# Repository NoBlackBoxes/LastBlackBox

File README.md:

# The Last Black Box

> - Do you depend on technology to work? to learn? to socialize?
> - Do you want to know what is going on inside the machines that run your life?
> - Do you want to be ready for the coming era of AI?

## Summary

Imagine a world without "black boxes". A world where you understand how your tools work and can use them to do what you want.

This world is much closer than you realize, and we have developed this training course to help get you there as quickly (and enjoyably!) as possible.

**The Last Black Box** is a hands-on introduction to the foundations of modern technology<p>...from ***electrons*** to ***AI***.

## Principles

----

<p align="center" style="font-size:32px">
<a href="course/README.md" style="color: #FFFF00; background: #000000; border-color: #FFFF00; border-style: solid; border-width: 2px; border-radius:6px; padding-left:12px; padding-right:12px;"><b>Start the course!</b></a>
</p>

----

## License

<br />The entire LastBlackBox repository and website is licensed under a <a rel="license" href="http://creativecommons.org/licenses/by-nc-sa/4.0/">Creative Commons Attribution-NonCommercial-ShareAlike 4.0 International License</a>.

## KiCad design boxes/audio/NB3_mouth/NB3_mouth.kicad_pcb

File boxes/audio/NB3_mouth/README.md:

# Audio : NB3_mouth

PCB design and fabrication for NB3 mouth, a mono i2s DAC and Amplifier

## Parts

- MAX98357A from Maxim: [datasheet](libraries/parts/I2S_DAC-AMP_MAX98357A/I2S_DAC-AMP_MAX98357A.pdf)

## Fabrication

### Generate files
0. Save front/back renders and 3D model (step)
1. Create "fab" folder in KiCAD project root
2. Export BOM (as CSV): File->Fabrication outputs->BOM
3. Edit BOM: Open as ODS and save as XLSX in "fab" folder
4. Generate Gerbers: File->Fabrication outputs->Gerbers [settings](NB3_mouth_FAB_plot_settings.png)
5. Generate Drill: File->Fabrication outputs->Drill Files [settings](NB3_mouth_FAB_drill_settings.png)
6. Generate Centroids: File->Fabrication outputs->Componenet Placement [settings](NB3_mouth_FAB_pos_settings.png)
7. Zip entire fab folder (including BOM.xlsx)

### Upload boards(s) - PCBWay

#### Assembly Service
- Service: Turnkey Assembly
- Board type: Panelized PCBs
- Assembly: Both Sides
- Quantity: *200*

##### Other Parameters
- Number of unique Parts: 6
- Number of SMD Parts: 6
- Number of BGA/QFP Parts: 1
- Number of Through-Hole Parts: 1
			
#### PCB Specifications
- Board type: Panel by PCBWay
- Panel requirements: Panel in 2*4, total 25 panels=total 200 individual boards.
- Route Process: Panel as Tab Route
- X-out Allowance in Panel: Accept
- Different design in panel: 1
- Size: 56 x 78 mm
- Quantity: 20
- Layer: 2 Layers
- Material: FR-4: TG150-160
- Thickness: 1.6 mm
- Min track/spacing: 6/6mil
- Min hole size: 0.3mm
- Solder mask: White
- Silkscreen: Black
- Edge connector: No
- Surface finish: Immersion gold(ENIG) (1U"), "HASL" to "ENIG" No
- Via process: Tenting vias
- Finished copper: 1 oz Cu
- Remove product No.: No

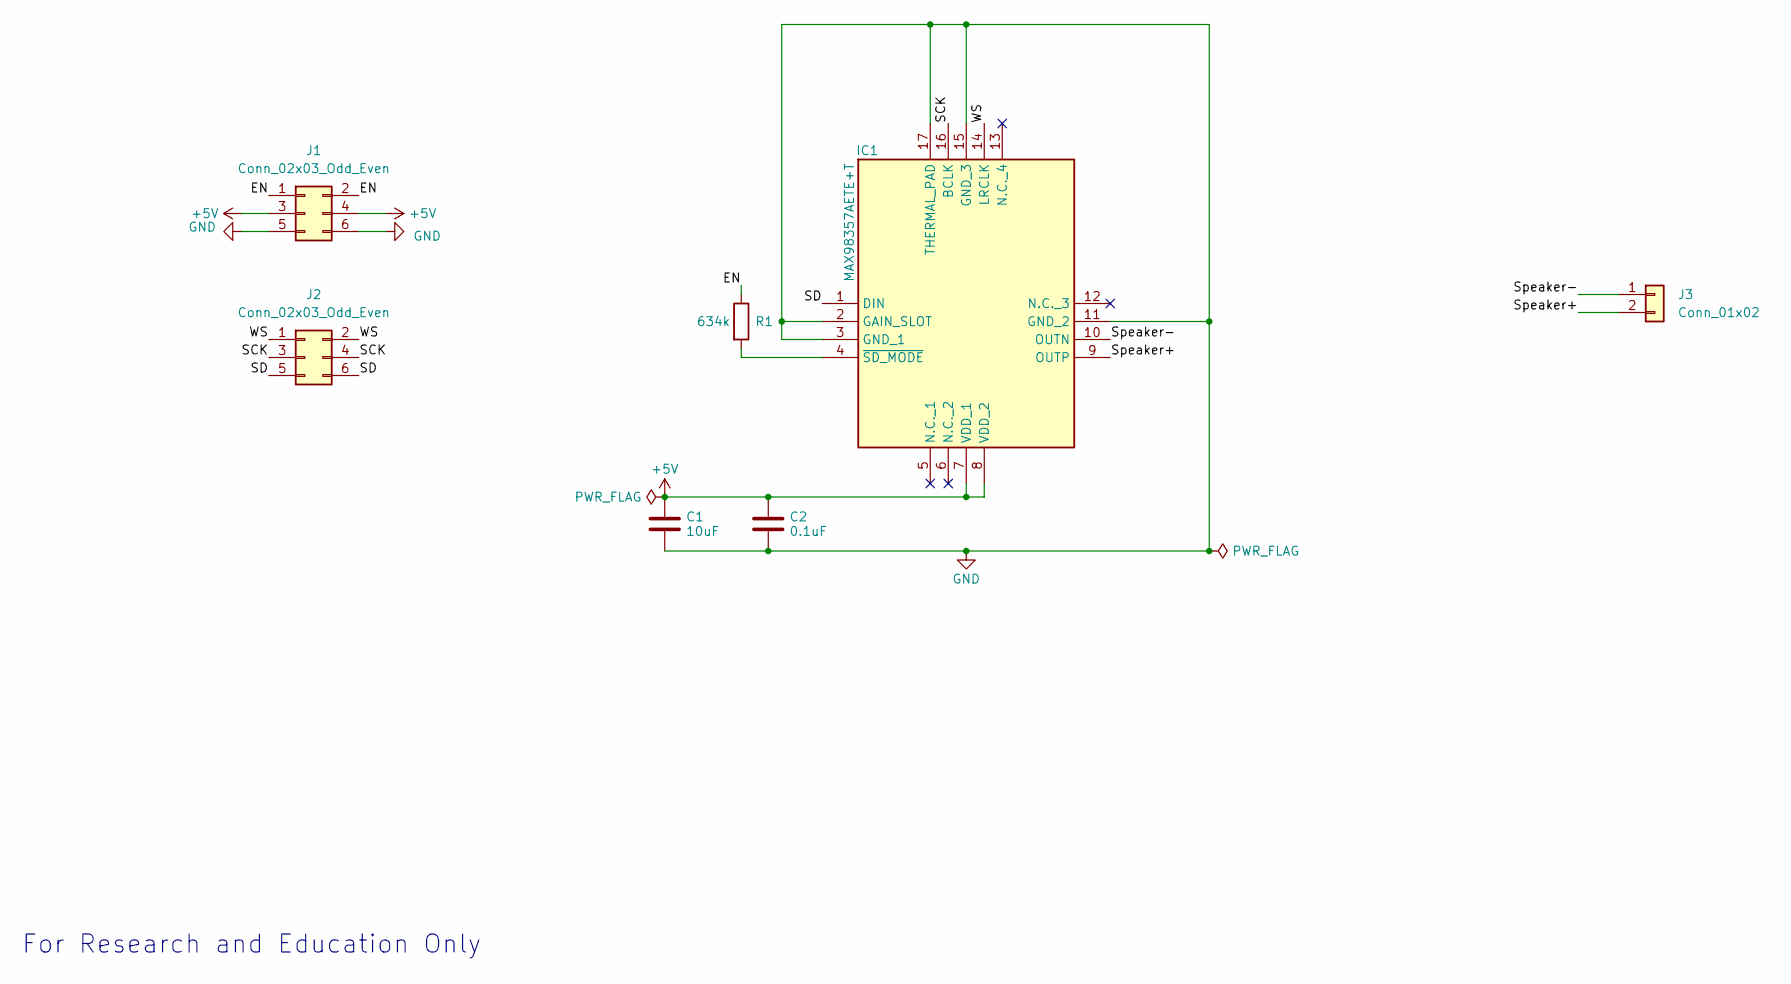
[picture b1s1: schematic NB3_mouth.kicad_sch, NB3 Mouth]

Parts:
C1: 10uF; C_0805_2012Metric
C2: 0.1uF; C_0402_1005Metric
IC1: MAX98357AETE+T; I2S_DAC-AMP_MAX98357A; Mouser Part Number 700-MAX98357AETE+T
J1, J2: Conn_02x03_Odd_Even; PinHeader_2x03_P2.54mm_Vertical_SMD
J3: Conn_01x02; PinHeader_1x02_P2.54mm_Horizontal
R1: 634k; R_0402_1005Metric

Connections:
+5V: C1.1, C2.1, IC1.7 (VDD_1), IC1.8 (VDD_2), J1.3, J1.4
/EN: J1.1, J1.2, R1.1
/SCK: IC1.16 (BCLK), J2.3, J2.4
/SD: IC1.1 (DIN), J2.5, J2.6
/Speaker+: IC1.9 (OUTP), J3.2
/Speaker-: IC1.10 (OUTN), J3.1
/WS: IC1.14 (LRCLK), J2.1, J2.2
GND: C1.2, C2.2, IC1.2 (GAIN_SLOT), IC1.3 (GND_1), IC1.11 (GND_2), IC1.15 (GND_3), IC1.17 (THERMAL_PAD), J1.5, J1.6
unnamed: IC1.4 (~SD_MODE), R1.2

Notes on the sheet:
For Research and Education Only

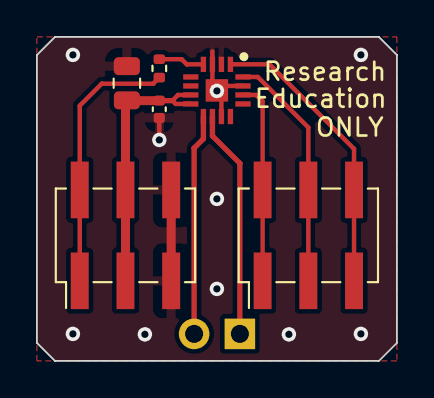
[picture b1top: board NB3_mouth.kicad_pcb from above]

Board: 2 copper layers, 20.0 x 18.0 mm, 7 parts (1 on the bottom side), 9 nets.

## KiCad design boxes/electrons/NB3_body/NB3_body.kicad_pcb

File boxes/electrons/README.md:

# The Last Black Box : Electrons
In this box, you will learn about electrons...

<details><summary><i>Materials</i></summary><p>

Name|Description| # |Package|Data|Link|
:-------|:----------|:-----:|:-:|:--:|:--:|
NB3 Body|NB3 robot base PCB|1|Body (000)|[-D-](/boxes/electrons/NB3_body)|[-L-](VK)
Resistor (470)|470 &Omega;/0.25 W|2|Passive Electronics|[-D-](/boxes/electrons/_resources/datasheets/resistor.pdf)|[-L-](https://uk.farnell.com/multicomp/mf25-470r/res-470r-1-250mw-axial-metal-film/dp/9341943)
Resistor (1k)|1 k&Omega;/0.25 W|2|Passive Electronics|[-D-](/boxes/electrons/_resources/datasheets/resistor.pdf)|[-L-](https://uk.farnell.com/multicomp/mf25-1k/res-1k-1-250mw-axial-metal-film/dp/9341102)
Resistor (10k)|10 k&Omega;/0.25 W|2|Passive Electronics|[-D-](/boxes/electrons/_resources/datasheets/resistor.pdf)|[-L-](https://uk.farnell.com/multicomp/mf25-10k/res-10k-1-250mw-axial-metal-film/dp/9341110)
Button|Tactile switch|2|Passive Electronics|[-D-](/boxes/electrons/_resources/datasheets/button.pdf)|[-L-](https://uk.farnell.com/omron/b3f-1000/switch-spno-0-05a-24v-tht-0-98n/dp/176432)
Potentiometer|2.2 k&Omega; variable resistor|2|Passive Electronics|[-D-](/boxes/electrons/_resources/datasheets/pot_2k2.pdf)|[-L-](https://uk.farnell.com/bourns/3362p-1-222lf/trimmer-pot-2-2kohm-10-1turn-th/dp/2328599)
Breadboard (400)|400-tie solderless breadboard|1|Small (010)|[-D-](/boxes/electrons/_resources/datasheets/breadboard_400.pdf)|[-L-](https://www.amazon.co.uk/gp/product/B0739XRX8F)
Breadboards (170)|170-tie solderless breadboard|4|Small (010)|[-D-](/boxes/electrons/_resources/datasheets/breadboard_170.pdf)|[-L-](https://www.amazon.co.uk/ELEGOO-tie-points-Breadboard-Breadboards-Electronic/dp/B01N0YWIR7)
Batteries (AA)|AA 1.5 V alkaline battery|4|Auxiliary|[-D-](/boxes/electrons/)|[-L-](https://www.amazon.co.uk/Duracell-Optimum-Alkaline-Batteries-MX1500/dp/B093Q5XY66)
Battery holder|4xAA battery holder with ON-OFF switch|1|Small (010)|[-D-](/boxes/electrons/)|[-L-](https://www.amazon.co.uk/gp/product/B0814ZH68F)
Jumper Kit|Kit of multi-length 22 AWG breadboard jumpers|1|Large (100)|[-D-](/boxes/electrons/_resources/datasheets/jumper_kit.pdf)|[-L-](https://uk.farnell.com/multicomp/mc001810/hard-jumper-wire-22awg-140pc/dp/2770338)
Jumper Wires|Assorted 22 AWG jumper wire leads (male/female)|1|Cables (001)|[-D-](/boxes/electrons/_resources/datasheets/jumper_wires.pdf)|[-L-](https://www.amazon.co.uk/gp/product/B09KR7Z4PF)
Test Lead|Alligator clip to 0.64 mm pin (20 cm)|2|Cables (001)|[-D-](/boxes/electrons/)|[-L-](https://www.amazon.co.uk/gp/product/B096JR15JW)
Rubber feet|Adhesive rubber standoffs (1421T6CL)|4|Passive Electronics|[-D-](/boxes/electrons/_resources/datasheets/rubber_feet.pdf)|[-L-](https://uk.farnell.com/hammond/1421t6cl/feet-stick-on-pk24/dp/1876522)
Capacitor (small)|0.1 uF ceramic capacitor|1|Passive Electronics|[-D-](/boxes/electrons/_resources/datasheets/capacitor_ceramic.pdf)|[-L-](https://uk.farnell.com/kemet/c322c104k1r5ta/cap-0-1-f-100v-10-x7r/dp/1457685)
Capacitor (large)|100 uF aluminum electrolytic capacitor|1|Passive Electronics|[-D-](/boxes/electrons/_resources/datasheets/capacitor_electrolytic.pdf)|[-L-](https://uk.farnell.com/rubycon/16zlh100mefc5x11/cap-100-f-16v-20/dp/8126283)

</p></details><hr>

## Electrons
#### Watch this video: [Electric Fields](https://vimeo.com/1032441712)
<p align="center">

</p>

> A very useful, and quite simple, depiction of the lines of force surrounding charged particles.

- Draw the electric field around a negative charge and positive charge separated by a small distance. Use the following image as a starting point.

#### Watch this video: [Voltage](https://vimeo.com/1000730032)
<p align="center">

</p>

> When there is more negative or positive charge in one location vs. another there is a *potential difference* between these locations. This *potential difference* is called a **voltage** and it creates a pressure that pushes electrons from the location with more negative charge to the location with less.

#### Watch this video: [Conductors](https://vimeo.com/1029337222)
<p align="center">

</p>

> Some materials have electrons in their outer orbitals that are happy to jump between neighboring atomic nuclei (of the same element). These electrons are "free" to move around the material. If we place such a material between two locations with a *potential difference* (voltage), then electrons will flow from the **(-)** location to the **(+)** location; the material will **conduct** electricity.

#### Watch this video: [Batteries](https://vimeo.com/1029278169)
<p align="center">

</p>

> Generating a stable voltage requires a renewable source of electrons to maintain a *potential difference*. We can accomplish this with a (redox) chemical reaction inside the wonderfully useful device that we call a **battery**.

- **TASK**: Measure the voltage of a AA battery using your multimeter.
  - *Hint*: Select the voltage ("V") setting and touch your probes to either end of the battery. Depending on your multimeter, you may also need to select an appropriate "range". For a single AA battery, you should expect to measure between 1 and 2 Volts.
  - *Help*: If you are new to using a multimeter, then I recommend that you watch this video: [NB3-Multimeter Basics](https://vimeo.com/1027764019)
  - *Help*: If you are new to measuring voltage with a multimeter, then I recommend that you watch this video: [NB3-Measuring Voltage](https://vimeo.com/1027762531)
> A single AA battery, fully charged, should have a voltage of ~1.6 Volts. If it is less than 1.5 Volts, then the battery is nearly *dead*.
- **TASK**: Measure the voltage of 4xAA batteries in series (end to end).
  - *Hint*: You can use your battery holder.
> Batteries connected in series will sum their voltages. You should measure four times the voltage of a single AA battery, ~6.4 Volts, from the batteries in your 4xAA holder.

#### Watch this video: [NB3 : Multimeter Basics](https://vimeo.com/1027764019)
<p align="center">

</p>

> An overview of digital multimeters for beginners. What can it measure? What features do you need to complete the course?

### NB3 : How Do Multimeters Work
> Learn how multimeters actually work

#### Watch this video: [NB3 : Measuring Voltage](https://vimeo.com/1027762531)
<p align="center">

</p>

> How to measure voltage with a digital multimeter.

#### Watch this video: [Current](https://vimeo.com/1029334167/2492ff3542)
<p align="center">

</p>

> The rate at which electrons flow, measured as *#charges / second*, is called **current**. We use the unit *Amps* (A) and the circuit symbol **I**.

#### Watch this video: [Resistors](https://vimeo.com/1029696806)
<p align="center">

</p>

> Many materials hold onto their outer electrons and resist their movement. We can create mixtures of these "resisting" materials and better "conducting" materials, often in the form of ceramics, to create **resistors** with a range of different *resistance* values, which we measure in Ohms (&Omega;).

- **TASK**: Measure the resistance of your resistors.
  - *Help*: If you are new to measuring resistance with a multimeter, then I recommend that you watch this video: [NB3-Measuring Resistance](https://vimeo.com/1027761453)
> Your kit contains 470 &Omega;, 1 k&Omega;, and 10 k&Omega; resistors. You should measure these values.

#### Watch this video: [NB3 : Measuring Resistance](https://vimeo.com/1027761453)
<p align="center">

</p>

> How to measure resistance with a digital multimeter.

#### Watch this video: [NB3 : Measuring Current](https://vimeo.com/1027757287)
<p align="center">

</p>

> How to measure current with a digital multimeter.

#### Watch this video: [NB3 : Body](https://vimeo.com/1030776673)
<p align="center">

</p>

> We will now start measuring and manipulating electricity, but first we will assemble a "prototyping platform" that also happens to be the **body** of your robot (NB3).

- **TASK**: Assemble the robot body (prototyping base board).
  - *Challenge*: If you are curious how the *NB3 Body* printed circuit board (PCB) was designed, then you can find the KiCAD files here: [NB3 Body PCB](/boxes/electrons/NB3_body).
> Your NB3 should now look like [this](/boxes/electrons/NB3_body/NB3_body_front.png). Your breadboards will be different colors...and you should have some rubber feet on the back.

#### Watch this video: [NB3 : Building Circuits](https://vimeo.com/1030783826)
<p align="center">

</p>

> With a voltage source (battery) and resistors, then we can start building "circuits" - complete paths of conduction that allow current to flow from a location with *less* electrons **(+)** to a location with *more* electrons **(-)**.

- *Note*: This is *weird*. Electrons are the things moving. Shouldn't we say that current "flows" from the **(-)** area to the **(+)** area? Unfortunately, current was described before anyone knew about electrons and we are stuck with the following awkward convention: **Current is defined to flow from (+) to (-)**...even though we now know that electrons are moving the opposite direction.
- **TASK**: Build the simple circuit below and measure the current flowing when you connect the battery pack.
  - *Warning*: Measuring current with a multimeter is ***tricky***. You can only get an accurate measurement if ***ALL*** of the current in the circuit is forced to flow through your multimeter. This means that when measuring current, your multimeter must be in *series* with the rest of the circuit. (As opposed to measuring voltage, when your multimeter is placed "parallel" to the circuit.)
  - *Help*: If you are new to measuring current with a multimeter, then I recommend you watch this video: [NB3-Measuring Current](https://vimeo.com/1027757287).
> Not too much current...and do not break your multimeter.

#### Watch this video: [Ohm's Law](https://vimeo.com/1029695302)
<p align="center">

</p>

> Ohm's Law describes the relationship between Voltage, Current, and Resistance. It is not complicated, but it is very useful.

- **TASK**: Does Ohm's Law hold? You know the voltage of the batteries (V) and the resistance of the resistor (R). Measure the current flowing (I) for different resistors and confirm that V = I*R.
> For the resistors in your kit, then Ohm's Law should determine the current that you measure.

#### Watch this video: [Voltage Dividers](https://vimeo.com/1030787469)
<p align="center">

</p>

> Controlling the level of voltage at different places in a circuit is critical to designing electronic devices.

- **TASK**: Build a voltage divider using two resistors of the same value. Measure the intermediate voltage (between the resistors).
> With equal size resistors, the intermediate voltage you measure should be half of the supply voltage.
- **TASK**: Build a voltage divider using a variable resistor (potentiometer). Measure the intermediate voltage. What happens when you change the position of the internal contact of the variable resistor (by turning the screw)?
  - *Help*: A video guide to completing these tasks can be found here: [NB3-Building Voltage Dividers](https://vimeo.com/1030790826)
> The intermediate voltage should vary continuously as you adjust the potentiometer.

#### Watch this video: [NB3 : Building Voltage Dividers](https://vimeo.com/1030790826)
<p align="center">

</p>

> Step-by-step guide to building and testing voltage dividers with discrete resistors and a potentiometer.

#### Watch this video: [Power](https://vimeo.com/1029693122)
<p align="center">

</p>

> When electrons move through a circuit, they deliver power (some amount of energy in some amount of time). This power can be used to do useful things: make a motor move, light a lamp, or generate heat. If we deliver too little power, then our electronic device may not work as designed. If we deliver too much, then it may never work again. We measure power in Watts.

#### Watch this video: [Capacitors](https://vimeo.com/1035298931)
<p align="center">

</p>

> Two conductors separated by an insulator (but in close proximity) can interact through the electric field. If we put an external voltage across these conductors, then they will gradually accumulate charge until their own voltage matches the external potential. We say that these devices have an intrinsic capacity for storing charge and we call them **capacitors**.

# Projects
### NB3 : Designing PCBs With KiCAD
> What is KiCAD and how can we use it to design (and manufacture) PCBs?

#### Watch this video: [NB3 : Building a Battery](https://vimeo.com/1029280971)
<p align="center">

</p>

> Let's build a version of the *first* battery, and use it to power an LED.

- **TASK**: Build a simple battery
  - Combine two different metals, one that oxidizes well and one that does not, and connect them together with a layer of electrolyte between (salt water soaked paper works fine, so does a piece of fruit).
> You should see a voltage if you choose your two metals wisely. Zinc and Copper should produce ~0.76 Volts. If you stack multiple cells in series, then the resulting voltage should sum.

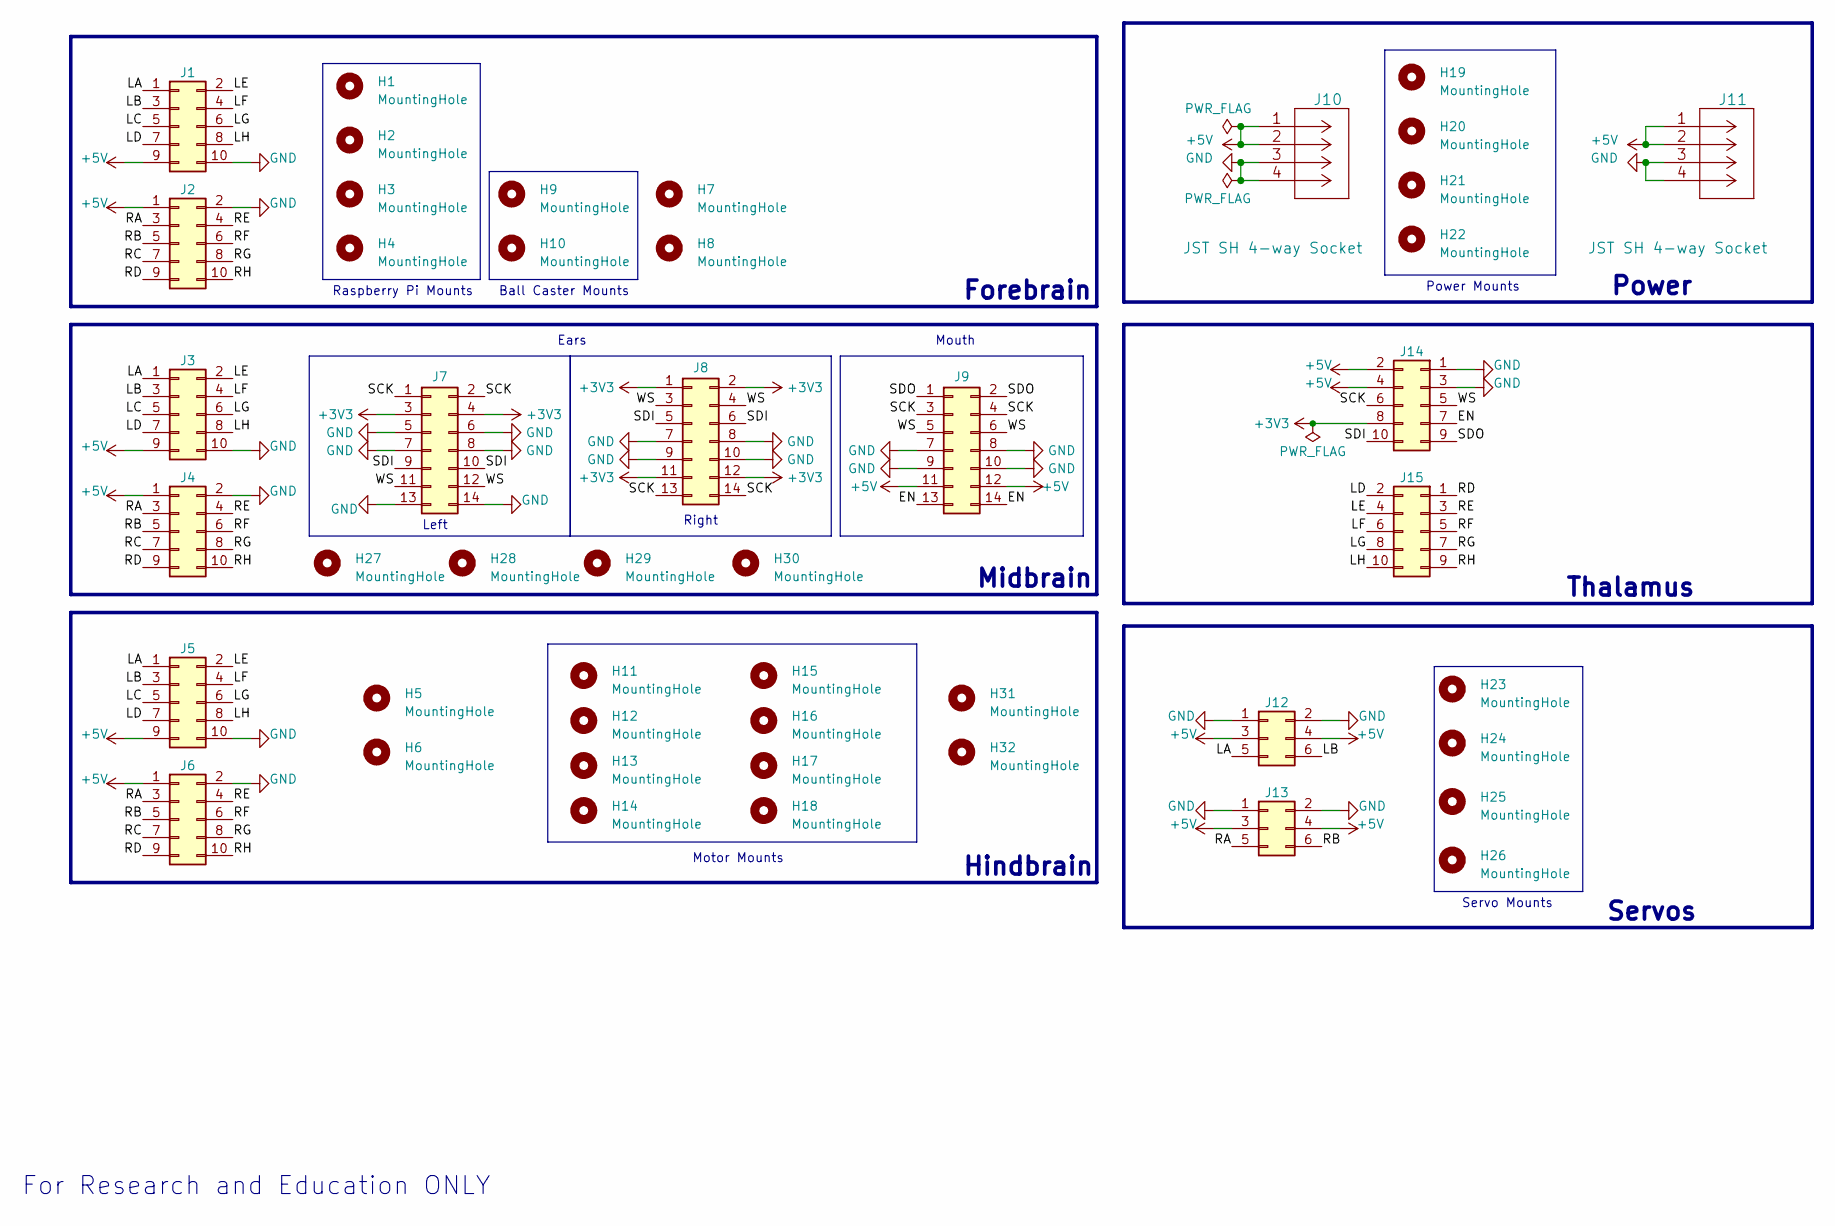
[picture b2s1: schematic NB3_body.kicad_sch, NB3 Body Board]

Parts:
H1, H2, H3, H4, H5, H6, H7, H8, H19, H20, H21, H22, H23, H24, H25, H26, H27, H28, H29, H30, H31, H32: MountingHole; MountingHole_2.7mm_M2.5_ISO7380_Pad
H9, H10: MountingHole; MountingHole_2.2mm_M2_ISO7380_Pad
H11, H12, H13, H14, H15, H16, H17, H18: MountingHole; MountingHole_3.2mm_M3_ISO7380_Pad
J1, J2, J3, J4, J5, J6, J14, J15: Conn_02x05_Counter_Clockwise; PinSocket_2x05_P2.54mm_Vertical_SMD
J7, J8, J9: Conn_02x07_Odd_Even; PinSocket_2x07_P2.54mm_Vertical_SMD
J10, J11: JST SH 4-way Socket; Connector_S4B-PH-SM4-TB(LF)(SN)
J12, J13: Conn_02x03_Top_Bottom; PinHeader_2x03_P2.54mm_Vertical

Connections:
+3V3: J7.3, J7.4, J8.1, J8.2, J8.11, J8.12, J14.8
+5V: J1.9, J2.1, J3.9, J4.1, J5.9, J6.1, J9.11, J9.12, J10.1, J10.2, J11.1, J11.2, J12.3, J12.4, J13.3, J13.4, J14.2, J14.4
/EN: J9.13, J9.14, J14.7
/LA: J1.1, J3.1, J5.1, J12.5
/LB: J1.3, J3.3, J5.3, J12.6
/LC: J1.5, J3.5, J5.5
/LD: J1.7, J3.7, J5.7, J15.2
/LE: J1.2, J3.2, J5.2, J15.4
/LF: J1.4, J3.4, J5.4, J15.6
/LG: J1.6, J3.6, J5.6, J15.8
/LH: J1.8, J3.8, J5.8, J15.10
/RA: J2.3, J4.3, J6.3, J13.5
/RB: J2.5, J4.5, J6.5, J13.6
/RC: J2.7, J4.7, J6.7
/RD: J2.9, J4.9, J6.9, J15.1
/RE: J2.4, J4.4, J6.4, J15.3
/RF: J2.6, J4.6, J6.6, J15.5
/RG: J2.8, J4.8, J6.8, J15.7
/RH: J2.10, J4.10, J6.10, J15.9
/SCK: J7.1, J7.2, J8.13, J8.14, J9.3, J9.4, J14.6
/SDI: J7.9, J7.10, J8.5, J8.6, J14.10
/SDO: J9.1, J9.2, J14.9
/WS: J7.11, J7.12, J8.3, J8.4, J9.5, J9.6, J14.5
GND: J1.10, J2.2, J3.10, J4.2, J5.10, J6.2, J7.5, J7.6, J7.7, J7.8, J7.13, J7.14, J8.7, J8.8, J8.9, J8.10, J9.7, J9.8, J9.9, J9.10, J10.3, J10.4, J11.3, J11.4, J12.1, J12.2, J13.1, J13.2, J14.1, J14.3

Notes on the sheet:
Ball Caster Mounts
Ears
Servo Mounts
Power
Thalamus
Servos
Hindbrain
Forebrain
Raspberry Pi Mounts
Motor Mounts
For Research and Education ONLY
Right
Midbrain
Left
Power Mounts
Mouth

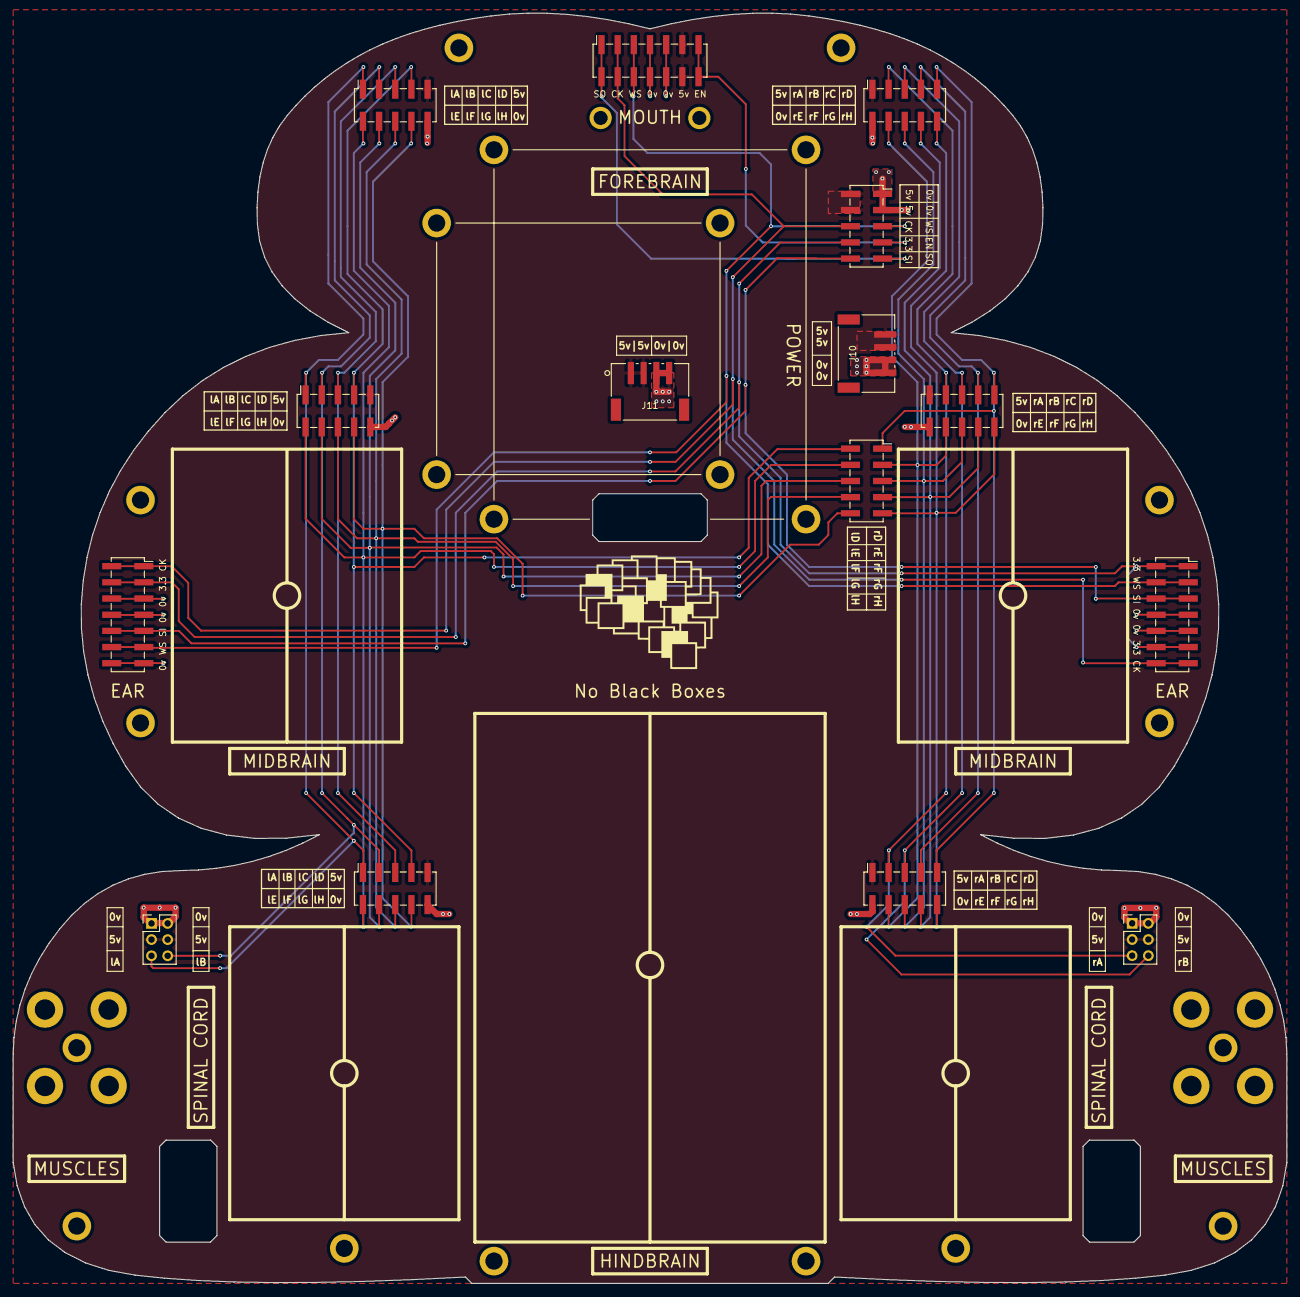
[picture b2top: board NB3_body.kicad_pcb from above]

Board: 2 copper layers, 200.0 x 199.5 mm, 47 parts (0 on the bottom side), 24 nets.

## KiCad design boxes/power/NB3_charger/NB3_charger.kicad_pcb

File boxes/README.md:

# Boxes

> A collection of **black boxes** and instructions for opening them.

----

## License

<br />The entire LastBlackBox repository and website is licensed under a <a rel="license" href="http://creativecommons.org/licenses/by-nc-sa/4.0/">Creative Commons Attribution-NonCommercial-ShareAlike 4.0 International License</a>.

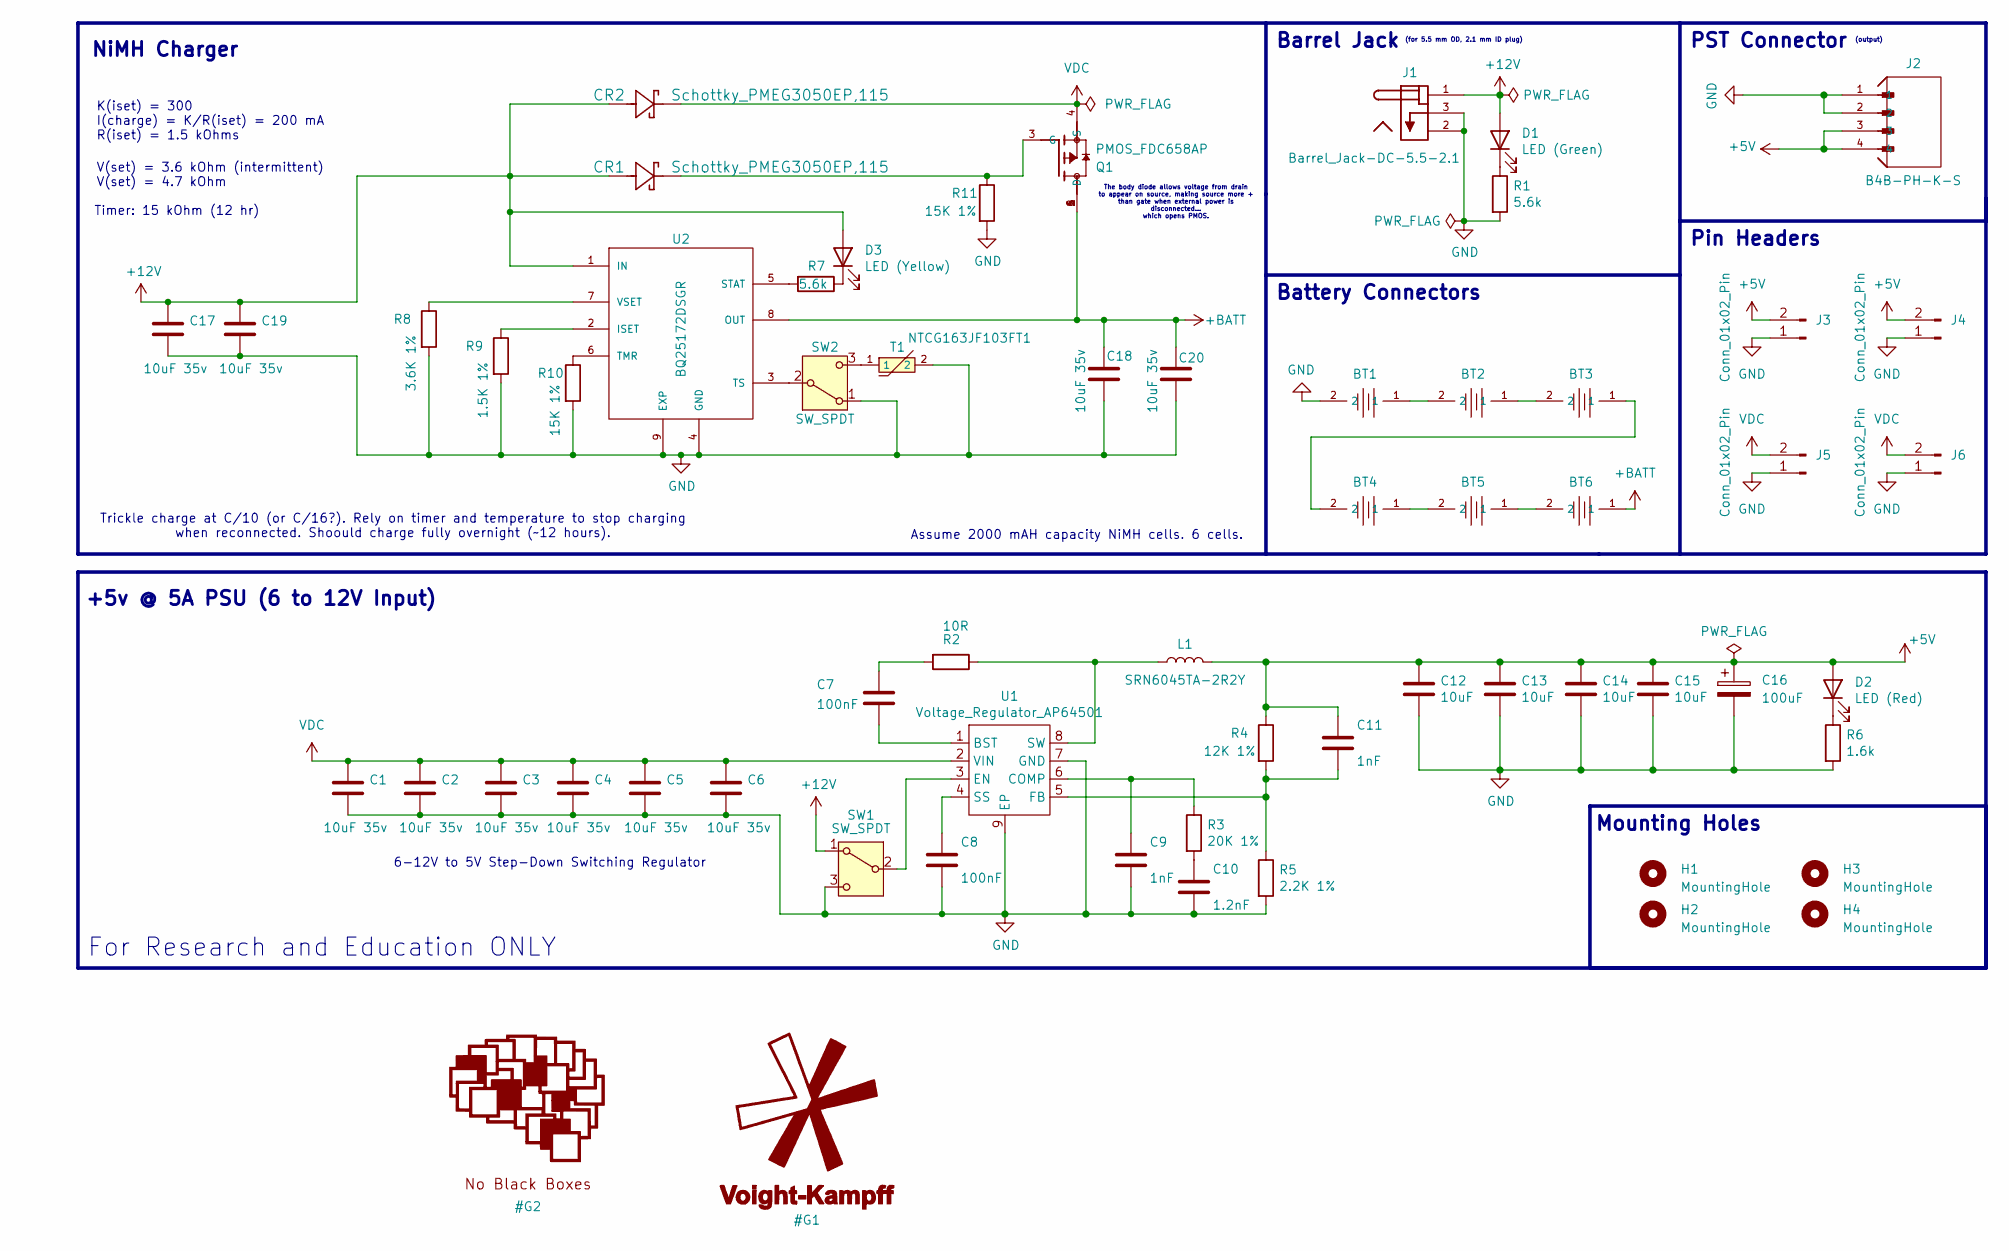
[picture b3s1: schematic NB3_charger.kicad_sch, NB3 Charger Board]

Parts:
BT1, BT2, BT3, BT4, BT5, BT6: 1028; AA_Battery_Holder_BH-AA-A5BJ012; PARTREV C; LCSC C5290180
C1, C2, C3, C4, C5, C6, C17, C18, C19, C20: 10uF 35v; C_0805_2012Metric; Part Description 10uF 10% or 20% 35V Ceramic Capacitor X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
C7, C8: 100nF; C_0402_1005Metric; Part Description 0.1uF 10% 16V Ceramic Capacitor X7R 040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
C9: 1nF; C_0402_1005Metric
C10: 1.2nF; C_0402_1005Metric; Part Description 1200pF 10% 10V Ceramic Capacitor X5R 04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
C11: 1nF; C_0402_1005Metric; Part Description 220 pF, 50 V, 0402 [1005 Metric], ± 5%,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
C12, C13, C14, C15: 10uF; C_0805_2012Metric; Part Description 10uF 10% 10V Ceramic Capacitor X7R 0805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
C16: 100uF; CP_EIA-7343-31_Kemet-D
CR1, CR2: Schottky_PMEG3050EP,115
D1: LED (Green); LED_0603_1608Metric
D2: LED (Red); LED_0603_1608Metric
D3: LED (Yellow); LED_0603_1608Metric
H1, H2, H3, H4: MountingHole; MountingHole_2.7mm_M2.5_ISO7380_Pad
J1: Barrel_Jack-DC-5.5-2.1; Barrel_Jack_TH_XUNPU_DC-005-A200; MPN DC-005-A200; LCSC C720557
J2: B4B-PH-K-S; Connector_B4B-PH-K-S(LF)(SN)
J3, J4, J5, J6: Conn_01x02_Pin; PinHeader_1x02_P2.54mm_Vertical
L1: SRN6045TA-2R2Y; L_Bourns_SRN6045TA; Part Description 3.3µH Semi-Shielded Wirewound Inductor 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
Q1: PMOS_FDC658AP; PMOS_SMD_FDC658AP
R1, R7: 5.6k; R_0402_1005Metric
R2: 10R; R_0402_1005Metric; Part Description Resistor 10R M1005 1% 63mW
R3: 20K 1%; R_0402_1005Metric; Part Description Resistor 20K M1005 1% 63mW
R4: 12K 1%; R_0402_1005Metric; Part Description Resistor 12K M1005 1% 63mW
R5: 2.2K 1%; R_0402_1005Metric; Part Description Resistor 2.2K M1005 1% 63mW
R6: 1.6k; R_0402_1005Metric
R8: 3.6K 1%; R_0402_1005Metric; Part Description Resistor 12K M1005 1% 63mW
R9: 1.5K 1%; R_0402_1005Metric; Part Description Resistor 12K M1005 1% 63mW
R10, R11: 15K 1%; R_0402_1005Metric; Part Description Resistor 12K M1005 1% 63mW
SW1, SW2: SW_SPDT; Switch_SPDT_SMD_Slide_JS102011JCQN
T1: NTCG163JF103FT1; Thermistor_NTC_NTCG163JF103FT1; LCSC C76589
U1: Voltage_Regulator_AP64501
U2: BQ25172DSGR; NiMH_Charger_BQ25172DSGR

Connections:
+5V: C11.1, C12.1, C13.1, C14.1, C15.1, C16.1, D2.2 (A), J2.3, J2.4, J3.2, J4.2, L1.2, R4.1
+12V: C17.1, C19.1, CR1.2, CR2.2, D1.2 (A), D3.2 (A), J1.1, SW1.1 (A), U2.1 (IN)
+BATT: BT6.1, C18.1, C20.1, Q1.1 (D), Q1.2 (D), Q1.5 (D), Q1.6 (D), U2.8 (OUT)
GND: BT1.2, C1.2, C2.2, C3.2, C4.2, C5.2, C6.2, C8.2, C9.2, C10.2, C12.2, C13.2, C14.2, C15.2, C16.2, C17.2, C18.2, C19.2, C20.2, J1.2, J1.3, J2.1, J2.2, J3.1, J4.1, J5.1, J6.1, R1.2, R5.2, R6.2, R8.2, R9.2, R10.2, R11.2, SW1.3 (C), SW2.1 (A), T1.2, U1.7 (GND), U1.9 (EP), U2.4 (GND), U2.9 (EXP), U2.10, U2.11
unnamed: BT1.1, BT2.2
unnamed: BT2.1, BT3.2
unnamed: BT3.1, BT4.2
unnamed: BT4.1, BT5.2
unnamed: BT5.1, BT6.2
unnamed: C7.1, R2.2
unnamed: C10.1, R3.2
unnamed: D1.1 (K), R1.1
unnamed: D2.1 (K), R6.1
unnamed: D3.1 (K), R7.1
unnamed: CR1.1, Q1.3 (G), R11.1
unnamed: SW1.2 (B), U1.3 (EN)
unnamed: SW2.2 (B), U2.3 (TS)
unnamed: SW2.3 (C), T1.1
unnamed: C7.2, U1.1 (BST)
unnamed: C9.1, R3.1, U1.6 (COMP)
unnamed: C11.2, R4.2, R5.1, U1.5 (FB)
unnamed: C8.1, U1.4 (SS)
unnamed: L1.1, R2.1, U1.8 (SW)
unnamed: R9.1, U2.2 (ISET)
unnamed: R7.2, U2.5 (STAT)
unnamed: R10.1, U2.6 (TMR)
unnamed: R8.1, U2.7 (VSET)
VDC: C1.1, C2.1, C3.1, C4.1, C5.1, C6.1, CR2.1, J5.2, J6.2, Q1.4 (S), U1.2 (VIN)

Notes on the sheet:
Timer: 15 kOhm (12 hr)
(output)
K(iset) = 300 I(charge) = K/R(iset) = 200 mA R(iset) = 1.5 kOhms
Pin Headers
The body diode allows voltage from drain to appear on source, making source more + than gate when external power is disconnected... which opens PMOS.
NiMH Charger
Mounting Holes
V(set) = 3.6 kOhm (intermittent) V(set) = 4.7 kOhm
(for 5.5 mm OD, 2.1 mm ID plug)
PST Connector
Trickle charge at C/10 (or C/16?). Rely on timer and temperature to stop charging when reconnected. Shoould charge fully overnight (~12 hours).
Battery Connectors
+5v @ 5A PSU (6 to 12V Input)
For Research and Education ONLY
Barrel Jack
Assume 2000 mAH capacity NiMH cells. 6 cells.
6-12V to 5V Step-Down Switching Regulator

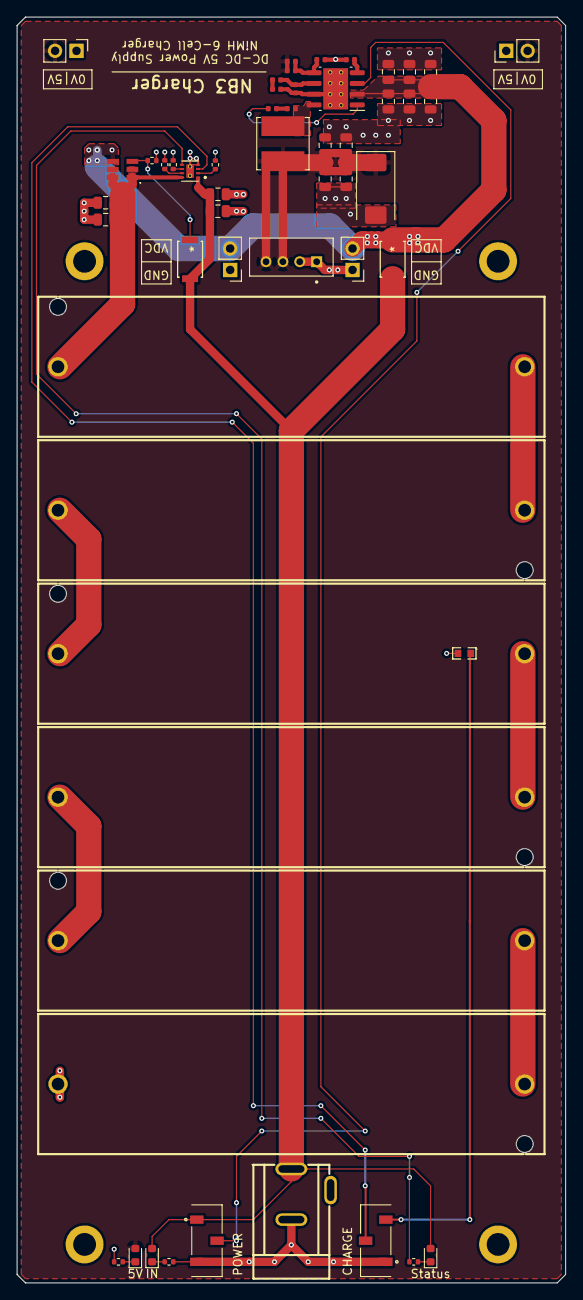
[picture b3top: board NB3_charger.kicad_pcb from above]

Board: 2 copper layers, 65.0 x 150.0 mm, 59 parts (0 on the bottom side), 28 nets.

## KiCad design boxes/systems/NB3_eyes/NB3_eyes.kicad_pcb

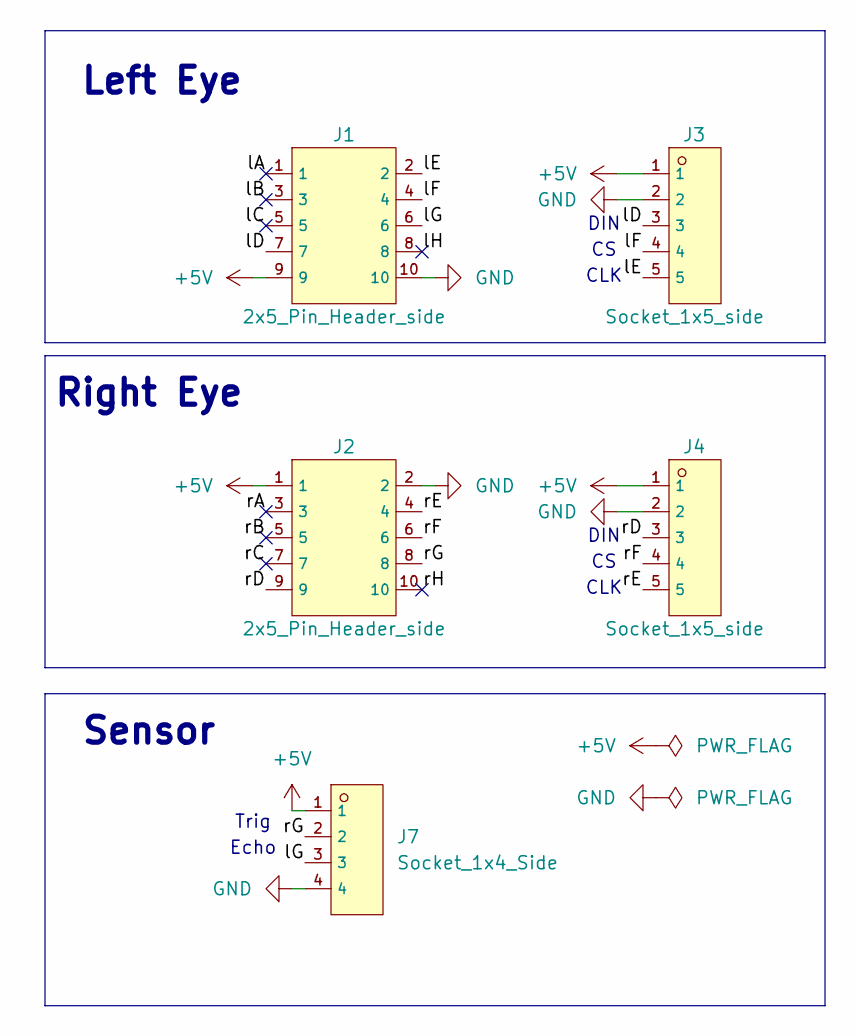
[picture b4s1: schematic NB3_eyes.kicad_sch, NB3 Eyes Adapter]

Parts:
J1, J2: 2x5_Pin_Header_side; PinHeader_Male_TH_Side_2x5_C60563; LCSC C60563
J3, J4: Socket_1x5_side; SocketHeader_Female_TH_Side_1x5_C2897387; LCSC C2897387
J7: Socket_1x4_Side; SocketHeader_Female_TH_Side_1x4_C5252508; LCSC C5252508

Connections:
+5V: J1.9, J2.1, J3.1, J4.1, J7.1
/lA: J1.1
/lB: J1.3
/lC: J1.5
/lD: J1.7, J3.3
/lE: J1.2, J3.5
/lF: J1.4, J3.4
/lG: J1.6, J7.3
/lH: J1.8
/rA: J2.3
/rB: J2.5
/rC: J2.7
/rD: J2.9, J4.3
/rE: J2.4, J4.5
/rF: J2.6, J4.4
/rG: J2.8, J7.2
/rH: J2.10
GND: J1.10, J2.2, J3.2, J4.2, J7.4

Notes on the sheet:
Trig
DIN
Echo
Right Eye
Sensor
CLK
Left Eye

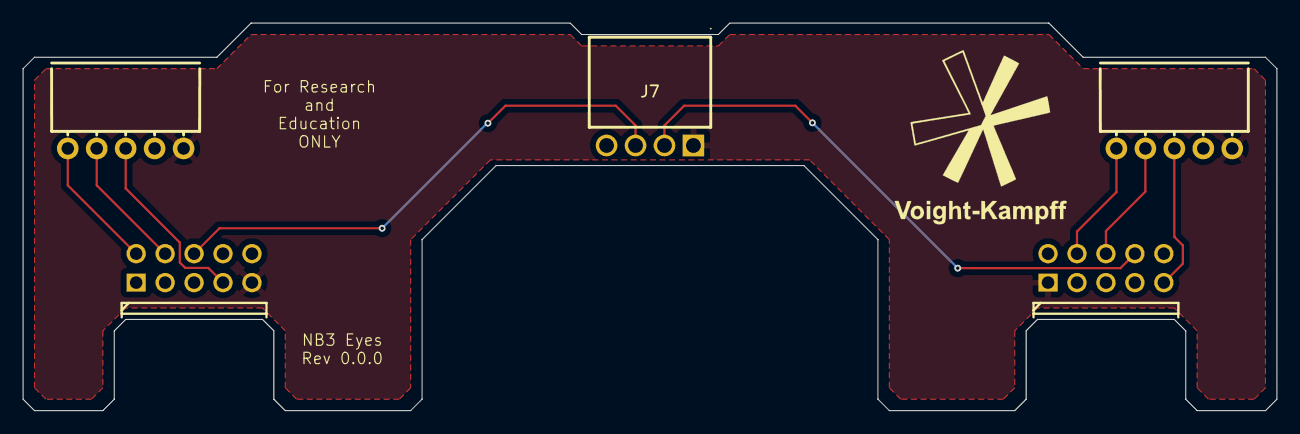
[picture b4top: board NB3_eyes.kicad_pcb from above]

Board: 2 copper layers, 110.0 x 34.0 mm, 5 parts (0 on the bottom side), 10 nets.

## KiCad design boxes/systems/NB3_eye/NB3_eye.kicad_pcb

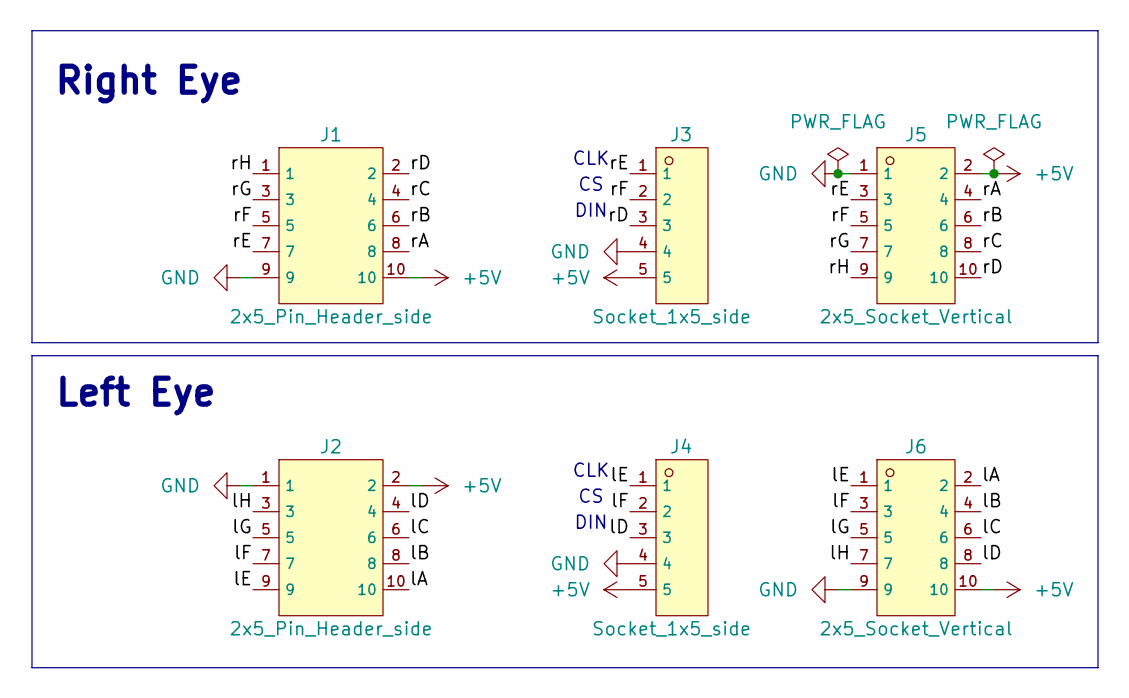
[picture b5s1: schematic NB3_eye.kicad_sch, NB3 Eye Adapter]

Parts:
J1, J2: 2x5_Pin_Header_side; PinHeader_Male_TH_Side_2x5_C60563; LCSC C60563
J3, J4: Socket_1x5_side; SocketHeader_Female_TH_Side_1x5_C2897387; LCSC C2897387
J5, J6: 2x5_Socket_Vertical; SocketHeader_Female_TH_2x5_C492399; LCSC C492399

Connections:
+5V: J1.10, J2.2, J3.5, J4.5, J5.2, J6.10
/lA: J2.10, J6.2
/lB: J2.8, J6.4
/lC: J2.6, J6.6
/lD: J2.4, J4.3, J6.8
/lE: J2.9, J4.1, J6.1
/lF: J2.7, J4.2, J6.3
/lG: J2.5, J6.5
/lH: J2.3, J6.7
/rA: J1.8, J5.4
/rB: J1.6, J5.6
/rC: J1.4, J5.8
/rD: J1.2, J3.3, J5.10
/rE: J1.7, J3.1, J5.3
/rF: J1.5, J3.2, J5.5
/rG: J1.3, J5.7
/rH: J1.1, J5.9
GND: J1.9, J2.1, J3.4, J4.4, J5.1, J6.9

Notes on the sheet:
DIN
Left Eye
CLK
Right Eye

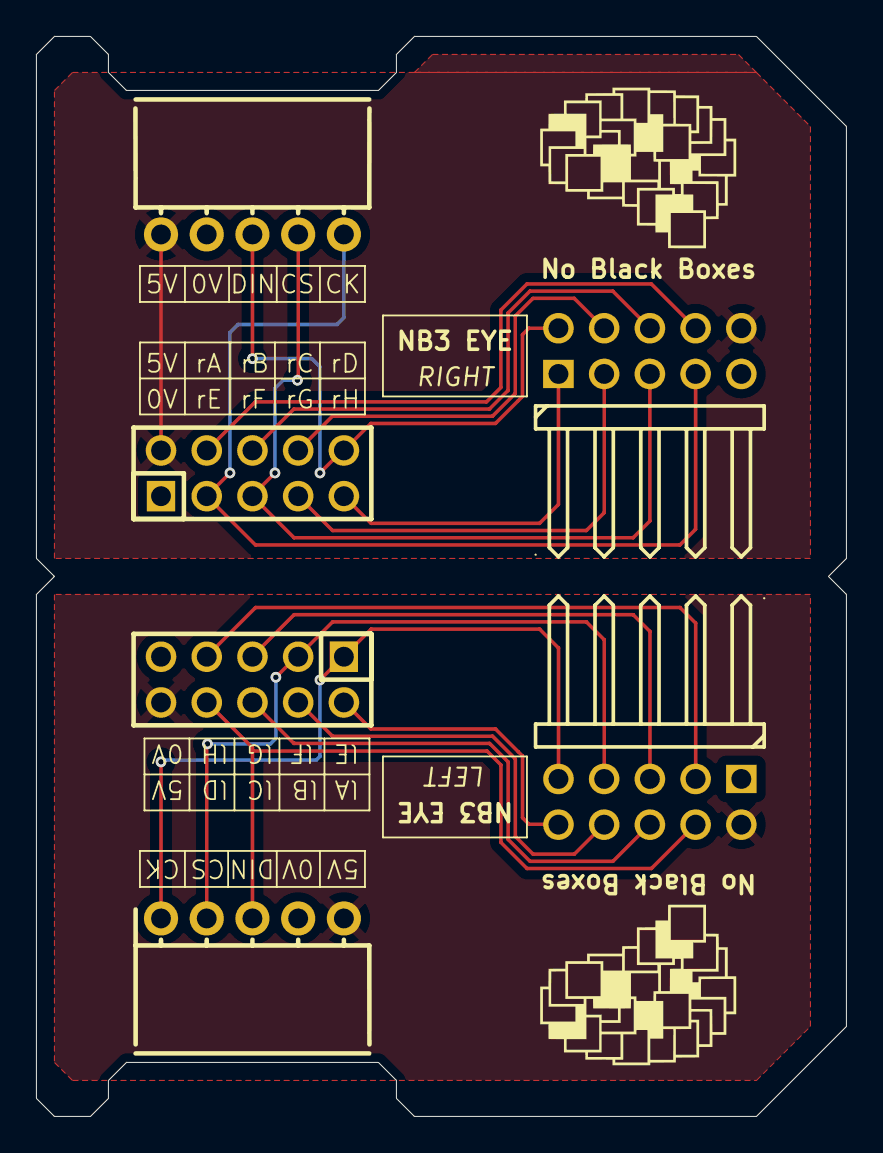
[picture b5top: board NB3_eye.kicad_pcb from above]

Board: 2 copper layers, 45.0 x 60.0 mm, 6 parts (0 on the bottom side), 18 nets.

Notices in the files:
parts and their libraries:
Copyright 2016 Accelerated Designs. All rights reserved.
